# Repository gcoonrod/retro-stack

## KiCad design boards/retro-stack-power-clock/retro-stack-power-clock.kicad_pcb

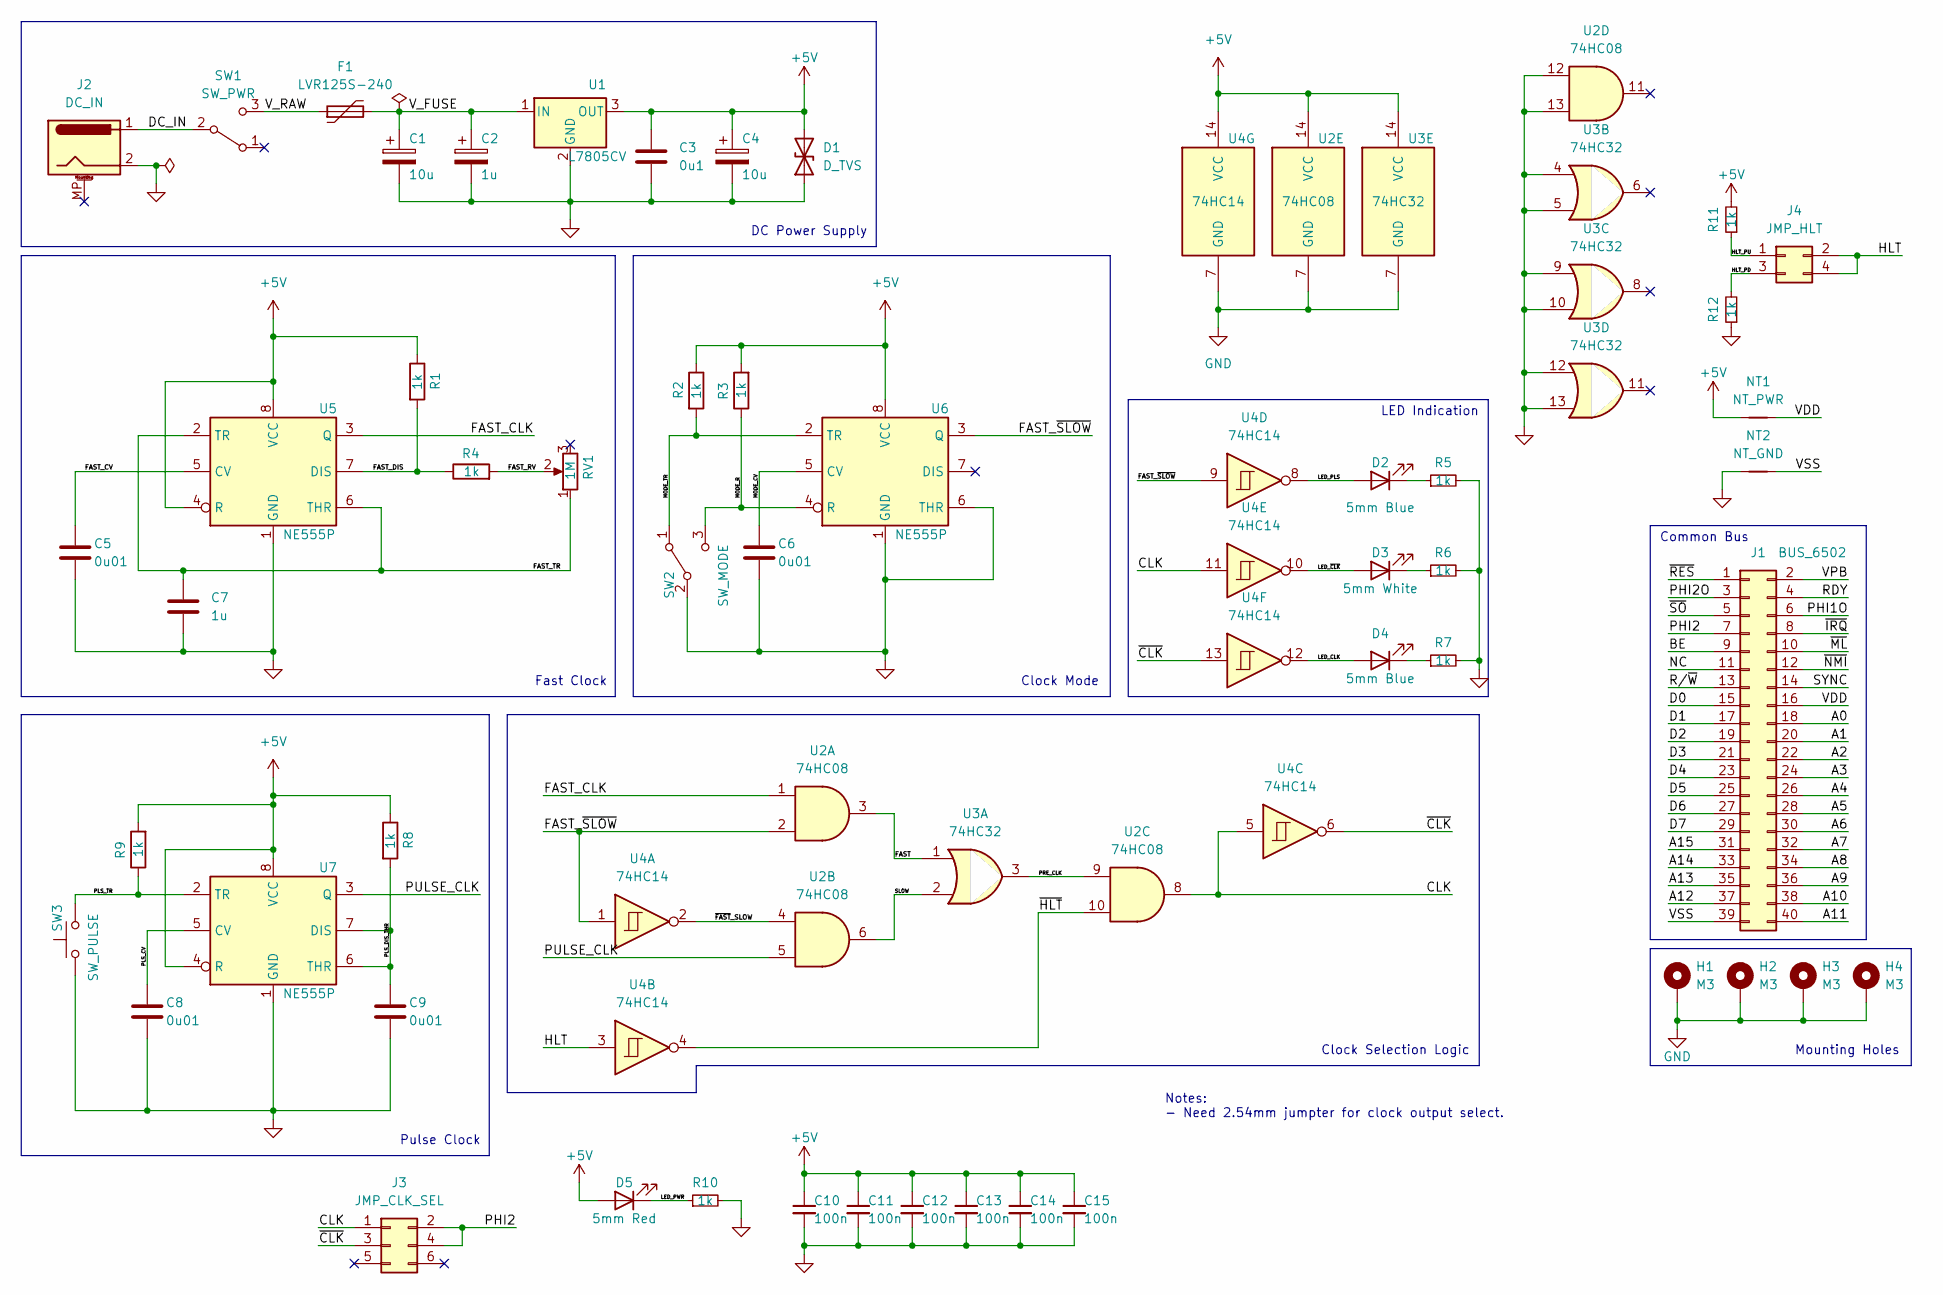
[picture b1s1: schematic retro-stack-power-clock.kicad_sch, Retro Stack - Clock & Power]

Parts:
C1, C4: 10u; CP_Radial_D5.0mm_P2.00mm; Mfr Part 50YXM10MEFR5X11
C2: 1u; CP_Radial_D5.0mm_P2.50mm; Mfr Part TAP105K050SCS
C3: 0u1; C_Rect_L7.0mm_W2.5mm_P5.00mm; Mfr Part K104K15X7RF53H5
C5, C6, C8, C9: 0u01; C_Rect_L7.0mm_W4.5mm_P5.00mm; Mfr Part FG28C0G1H103JNT06
C7: 1u; C_Rect_L4.6mm_W3.8mm_P2.50mm_MKS02_FKP02; Mfr Part FG18X7R1E105KRT06
C10, C11, C12, C13, C14, C15: 100n; C_Rect_L7.0mm_W2.5mm_P5.00mm; Mfr Part K104K15X7RF53H5
D1: D_TVS; D_DO-201_P5.08mm_Vertical_AnodeUp; Mfr Part 1.5KE6.8CA
D2, D4: 5mm Blue; LED_D5.0mm; Mfr Part SSL-LX5093USBD
D3: 5mm White; LED_D5.0mm; Mfr Part SSL-LX5093UWW
D5: 5mm Red; LED_D5.0mm; Mfr Part 151051RS11000
F1: LVR125S-240; LVR125S240; Mfr Part LVR125S-240
H1, H2, H3, H4: M3; MountingHole_3.2mm_M3_ISO7380_Pad
J1: BUS_6502; PinSocket_2x20_P2.54mm_Vertical; Mfr Part 61304021821
J2: DC_IN; BarrelJack_CUI_PJ-063AH_Horizontal; Mfr Part PJ-063AH
J3: JMP_CLK_SEL; PinHeader_2x03_P2.54mm_Vertical; Mfr Part 10129381-906002BLF
J4: JMP_HLT; PinHeader_2x02_P2.54mm_Vertical
NT1: NT_PWR; NetTie-2_SMD_Pad2.0mm
NT2: NT_GND; NetTie-2_SMD_Pad2.0mm
R1, R2, R3, R4, R5, R6, R7, R8, R9, R10, R11, R12: 1k; R_Axial_DIN0207_L6.3mm_D2.5mm_P10.16mm_Horizontal; Mfr Part MFR-25FBF52-1K
RV1: 1M; Potentiometer_Bourns_PTV09A-2_Single_Horizontal; Mfr Part PTV09A-2025F-B105
SW1: SW_PWR; EG1213; Mfr Part EG1213
SW2: SW_MODE; LC1258EENP1RLGR; Mfr Part LC1258EENP1RLGR
SW3: SW_PULSE; SW_Tactile_SPST_Angled_PTS645Vx58-2LFS; Mfr Part TS11-674-73-BK-100-RA-D
U1: L7805CV; TO-220-3_Horizontal_TabUp; Mfr Part L7805CV
U2: 74HC08; DIP-14_W7.62mm_Socket_LongPads; Mfr Part SN74HC08N
U3: 74HC32; DIP-14_W7.62mm_Socket_LongPads; Mfr Part SN74HC32N
U4: 74HC14; DIP-14_W7.62mm_Socket_LongPads; Mfr Part SN74HC14AN
U5, U6, U7: NE555P; DIP-8_W7.62mm_LongPads; Mfr Part NE555P

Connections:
+5V: C3.1, C4.1, C10.1, C11.1, C12.1, C13.1, C14.1, C15.1, D1.2 (A2), D5.2 (A), NT1.1, R1.1, R2.1, R3.2, R8.1, R9.2, R11.2, U1.3 (OUT), U2.14 (VCC), U3.14 (VCC), U4.14 (VCC), U5.4 (R), U5.8 (VCC), U6.8 (VCC), U7.4 (R), U7.8 (VCC)
/A0: J1.18
/A1: J1.20
/A2: J1.22
/A3: J1.24
/A4: J1.26
/A5: J1.28
/A6: J1.30
/A7: J1.32
/A8: J1.34
/A9: J1.36
/A10: J1.38
/A11: J1.40
/A12: J1.37
/A13: J1.35
/A14: J1.33
/A15: J1.31
/BE: J1.9
/CLK: J3.1, U2.8, U4.5, U4.11
/D0: J1.15
/D1: J1.17
/D2: J1.19
/D3: J1.21
/D4: J1.23
/D5: J1.25
/D6: J1.27
/D7: J1.29
/DC_IN: J2.1, SW1.2 (B)
/FAST: U2.3, U3.1
/FAST_CLK: U2.1, U5.3 (Q)
/FAST_CV: C5.1, U5.5 (CV)
/FAST_DIS: R1.2, R4.1, U5.7 (DIS)
/FAST_RV: R4.2, RV1.2
/FAST_TR: C7.1, RV1.1, U5.2 (TR), U5.6 (THR)
/FAST_~SLOW: U2.2, U4.1, U4.9, U6.3 (Q)
/HLT: J4.2, J4.4, U4.3
/HLT_PD: J4.3, R12.2
/HLT_PU: J4.1, R11.1
/LED_CLK: D4.2 (A), U4.12
/LED_PLS: D2.2 (A), U4.8
/LED_PWR: D5.1 (K), R10.1
/LED_~CLK: D3.2 (A), U4.10
/MODE_CV: C6.1, U6.5 (CV)
/MODE_R: R3.1, SW2.3 (C), U6.4 (R)
/MODE_TR: R2.2, SW2.1 (A), U6.2 (TR)
/NC: J1.11
/PHI1O: J1.6
/PHI2: J1.7, J3.2, J3.4
/PHI2O: J1.3
/PLS_CV: C8.1, U7.5 (CV)
/PLS_DIS_THR: C9.1, R8.2, U7.6 (THR), U7.7 (DIS)
/PLS_TR: R9.1, SW3.2, U7.2 (TR)
/PRE_CLK: U2.9, U3.3
/PULSE_CLK: U2.5, U7.3 (Q)
/RDY: J1.4
/R/~W: J1.13
/SLOW: U2.6, U3.2
/SYNC: J1.14
/VDD: J1.16, NT1.2
/VPB: J1.2
/VSS: J1.39, NT2.2
/V_FUSE: C1.1, C2.1, F1.2, U1.1 (IN)
/V_RAW: F1.1, SW1.3 (C)
/~CLK: J3.3, U4.6, U4.13
/~FAST_SLOW: U2.4, U4.2
/~HLT: U2.10, U4.4
/~IRQ: J1.8
/~ML: J1.10
/~NMI: J1.12
/~RES: J1.1
/~SO: J1.5
GND: C1.2, C2.2, C3.2, C4.2, C5.2, C6.2, C7.2, C8.2, C9.2, C10.2, C11.2, C12.2, C13.2, C14.2, C15.2, D1.1 (A1), H1.1, H2.1, H3.1, H4.1, J2.2, NT2.1, R5.2, R6.2, R7.2, R10.2, R12.1, SW2.2 (B), SW3.1, U1.2 (GND), U2.7 (GND), U2.12, U2.13, U3.4, U3.5, U3.7 (GND), U3.9, U3.10, U3.12, U3.13, U4.7 (GND), U5.1 (GND), U6.1 (GND), U6.6 (THR), U7.1 (GND)
unnamed: D2.1 (K), R5.1
unnamed: D3.1 (K), R6.1
unnamed: D4.1 (K), R7.1

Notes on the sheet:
Pulse Clock
Fast Clock
Common Bus
LED Indication
Notes: - Need 2.54mm jumpter for clock output select.
DC Power Supply
Mounting Holes
Clock Mode
Clock Selection Logic

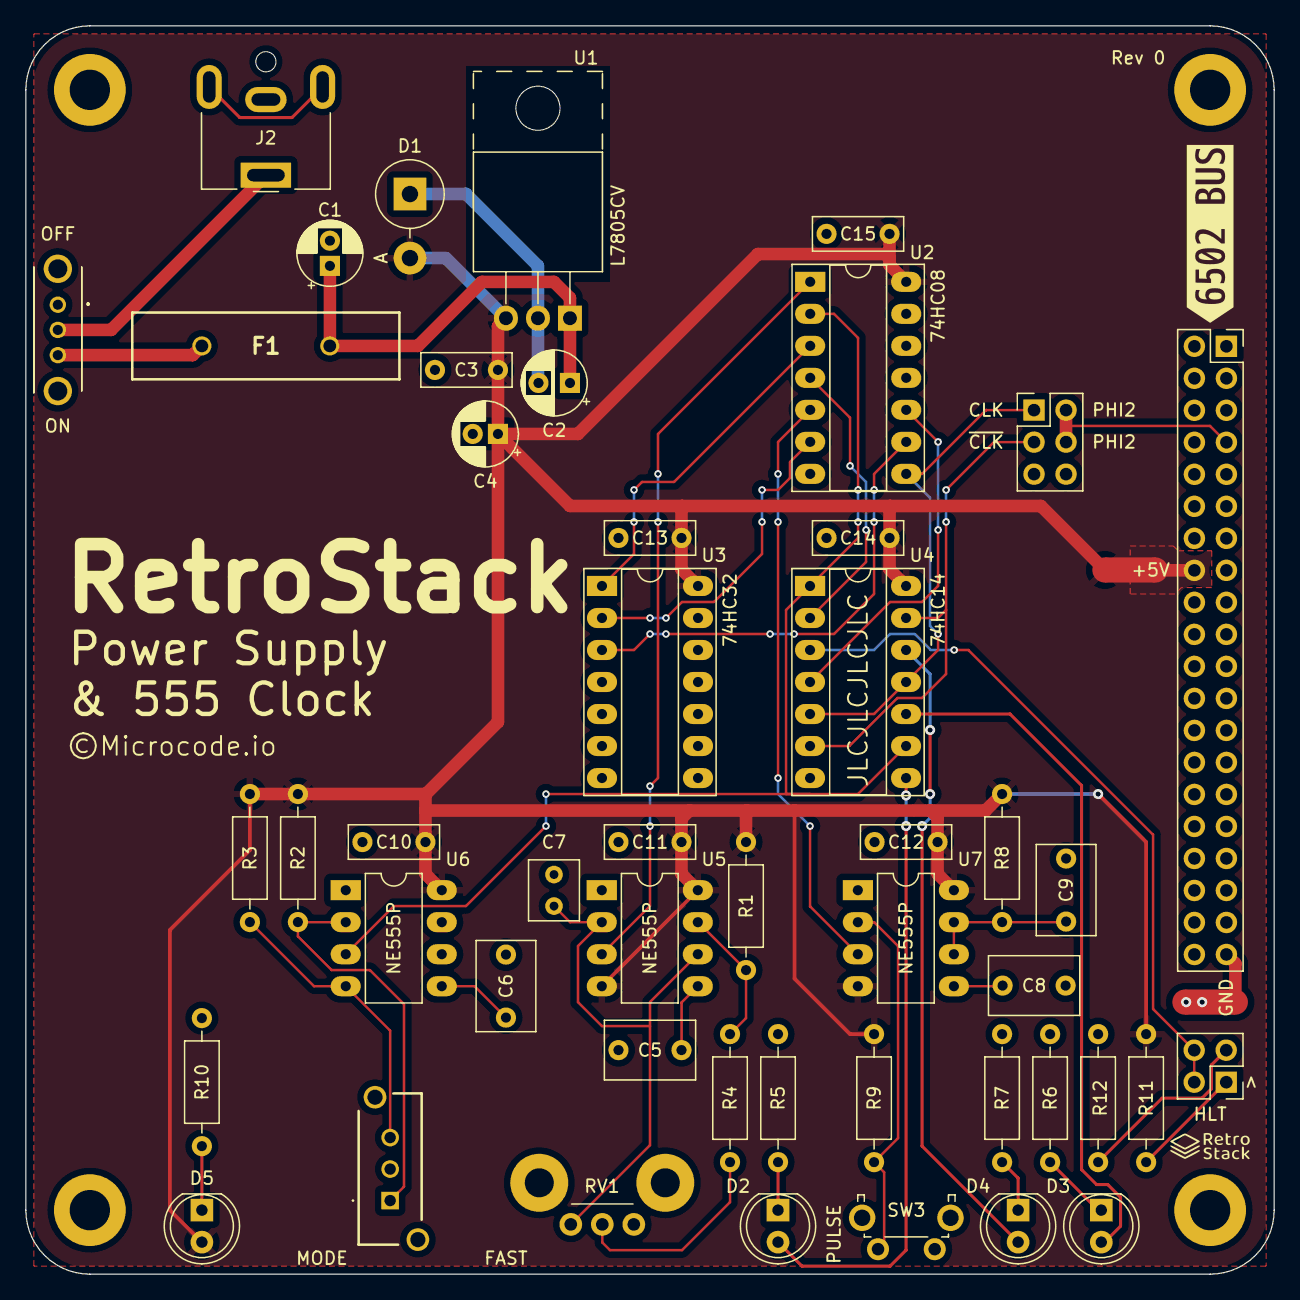
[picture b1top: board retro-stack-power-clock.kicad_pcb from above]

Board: 2 copper layers, 99.1 x 99.1 mm, 55 parts (0 on the bottom side), 38 nets.

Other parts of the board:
kibuzzard-642888DE: G***; kibuzzard-642888DE

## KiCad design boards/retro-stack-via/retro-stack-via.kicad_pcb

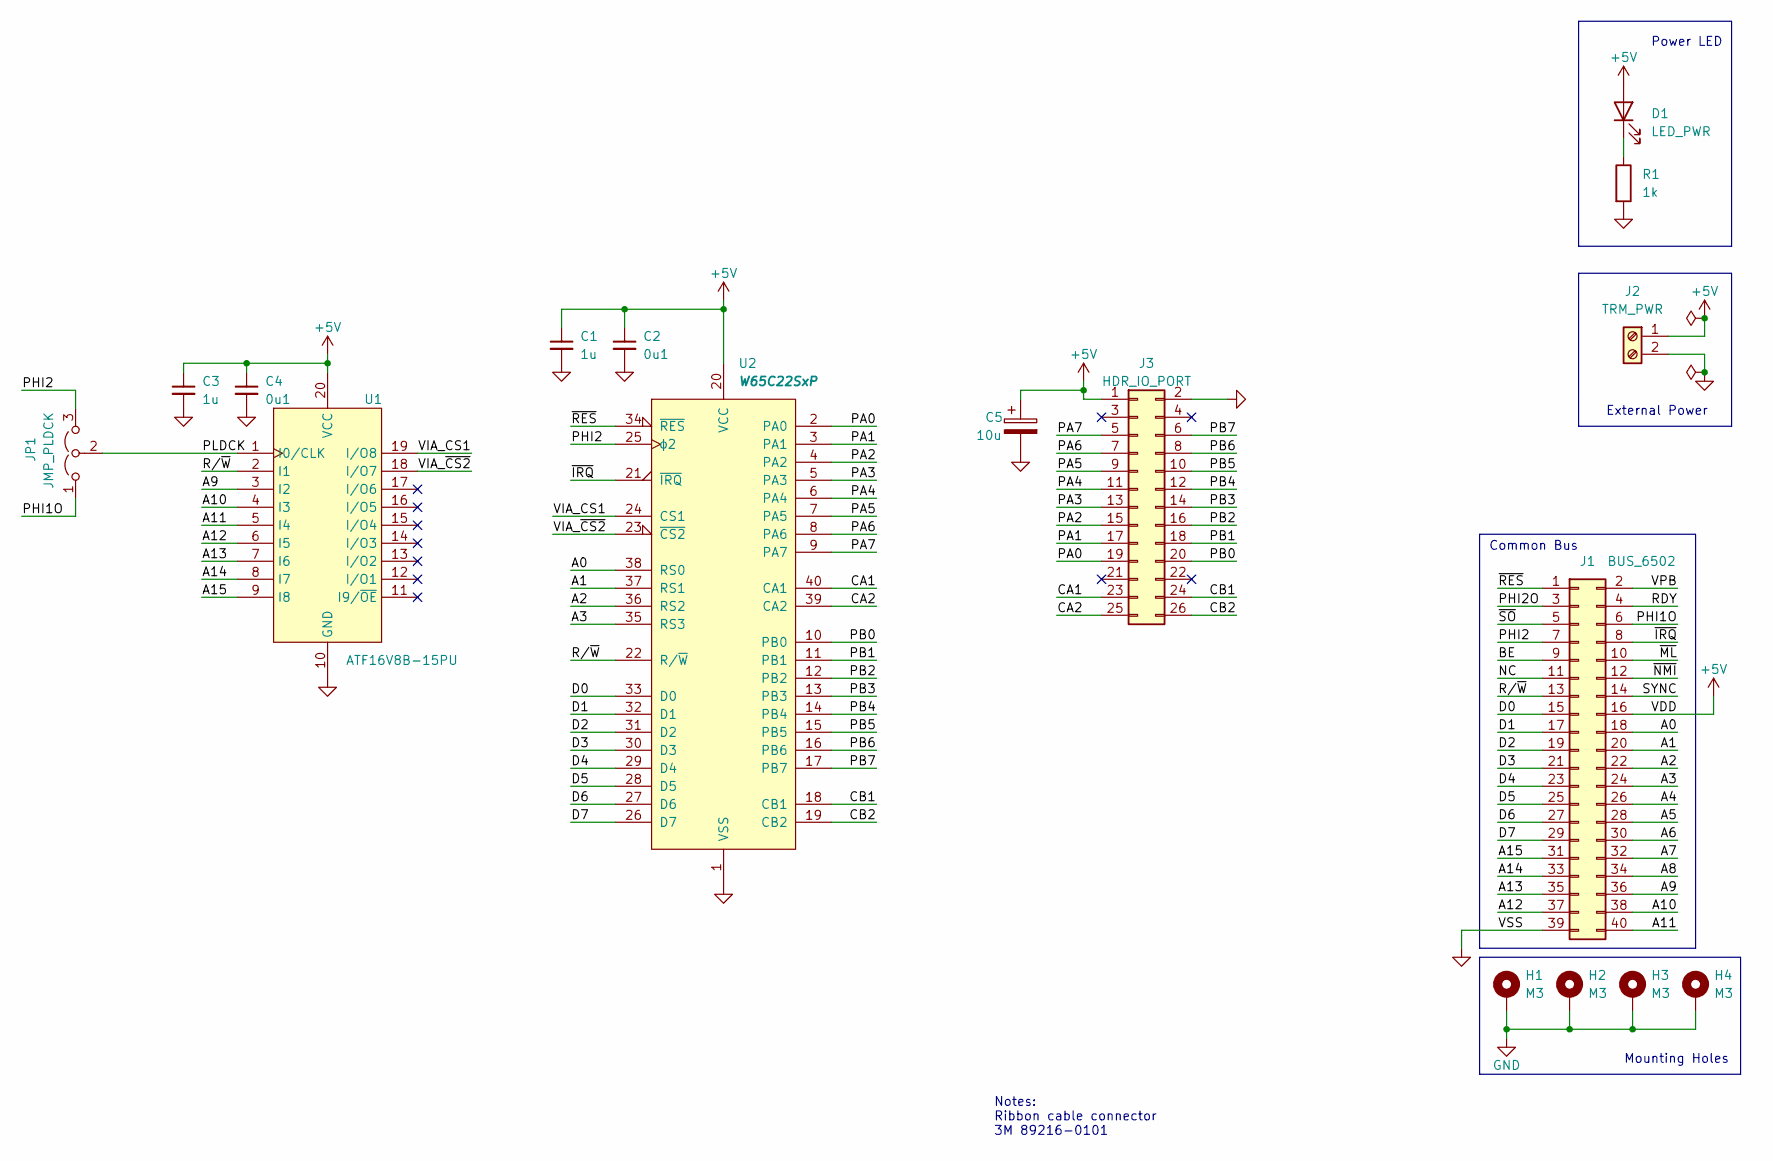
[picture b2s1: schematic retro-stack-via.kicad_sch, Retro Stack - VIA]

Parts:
C1, C3: 1u; C_Rect_L4.0mm_W2.5mm_P2.50mm; Mfr Part FA18X7R1E105KRU06
C2, C4: 0u1; C_Rect_L4.0mm_W2.5mm_P2.50mm; Mfr Part RCER71E104K0A2H03B
C5: 10u; CP_Radial_D5.0mm_P2.50mm
D1: LED_PWR; LED_D5.0mm
H1, H2, H3, H4: M3; MountingHole_3.2mm_M3_ISO7380_Pad
J1: BUS_6502; PinSocket_2x20_P2.54mm_Vertical
J2: TRM_PWR; TerminalBlock_Phoenix_MPT-0,5-2-2.54_1x02_P2.54mm_Horizontal; Mfr Part 1725656
J3: HDR_IO_PORT; IDC-Header_2x13_P2.54mm_Vertical; Mfr Part 30326-6002HB
JP1: JMP_PLDCK; PinHeader_1x03_P2.54mm_Vertical; Mfr Part M7581-05
R1: 1k; R_Axial_DIN0204_L3.6mm_D1.6mm_P5.08mm_Horizontal
U1: ATF16V8B-15PU; DIP-20_W7.62mm_Socket_LongPads; Mfr Part ATF16V8B-15PU
U2: W65C22SxP; DIP-40_W15.24mm_Socket_LongPads

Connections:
+5V: C1.1, C2.1, C3.1, C4.1, C5.1, D1.2 (A), J1.16, J2.1, J3.1, U1.20 (VCC), U2.20 (VCC)
/A0: J1.18, U2.38 (RS0)
/A1: J1.20, U2.37 (RS1)
/A2: J1.22, U2.36 (RS2)
/A3: J1.24, U2.35 (RS3)
/A4: J1.26
/A5: J1.28
/A6: J1.30
/A7: J1.32
/A8: J1.34
/A9: J1.36, U1.3 (I2)
/A10: J1.38, U1.4 (I3)
/A11: J1.40, U1.5 (I4)
/A12: J1.37, U1.6 (I5)
/A13: J1.35, U1.7 (I6)
/A14: J1.33, U1.8 (I7)
/A15: J1.31, U1.9 (I8)
/BE: J1.9
/CA1: J3.23, U2.40 (CA1)
/CA2: J3.25, U2.39 (CA2)
/CB1: J3.24, U2.18 (CB1)
/CB2: J3.26, U2.19 (CB2)
/D0: J1.15, U2.33 (D0)
/D1: J1.17, U2.32 (D1)
/D2: J1.19, U2.31 (D2)
/D3: J1.21, U2.30 (D3)
/D4: J1.23, U2.29 (D4)
/D5: J1.25, U2.28 (D5)
/D6: J1.27, U2.27 (D6)
/D7: J1.29, U2.26 (D7)
/NC: J1.11
/PA0: J3.19, U2.2 (PA0)
/PA1: J3.17, U2.3 (PA1)
/PA2: J3.15, U2.4 (PA2)
/PA3: J3.13, U2.5 (PA3)
/PA4: J3.11, U2.6 (PA4)
/PA5: J3.9, U2.7 (PA5)
/PA6: J3.7, U2.8 (PA6)
/PA7: J3.5, U2.9 (PA7)
/PB0: J3.20, U2.10 (PB0)
/PB1: J3.18, U2.11 (PB1)
/PB2: J3.16, U2.12 (PB2)
/PB3: J3.14, U2.13 (PB3)
/PB4: J3.12, U2.14 (PB4)
/PB5: J3.10, U2.15 (PB5)
/PB6: J3.8, U2.16 (PB6)
/PB7: J3.6, U2.17 (PB7)
/PHI1O: J1.6, JP1.1 (A)
/PHI2: J1.7, JP1.3 (B), U2.25 (ϕ2)
/PHI2O: J1.3
/PLDCK: JP1.2 (C), U1.1 (I0/CLK)
/RDY: J1.4
/R/~W: J1.13, U1.2 (I1), U2.22 (R/~W)
/SYNC: J1.14
/VIA_CS1: U1.19 (I/O8), U2.24 (CS1)
/VIA_~CS2: U1.18 (I/O7), U2.23 (~CS2)
/VPB: J1.2
/~IRQ: J1.8, U2.21 (~IRQ)
/~ML: J1.10
/~NMI: J1.12
/~RES: J1.1, U2.34 (~RES)
/~SO: J1.5
GND: C1.2, C2.2, C3.2, C4.2, C5.2, H1.1, H2.1, H3.1, H4.1, J1.39, J2.2, J3.2, R1.2, U1.10 (GND), U2.1 (VSS)
unnamed: D1.1 (K), R1.1

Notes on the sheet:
Notes: Ribbon cable connector 3M 89216-0101
External Power
Common Bus
Power LED
Mounting Holes

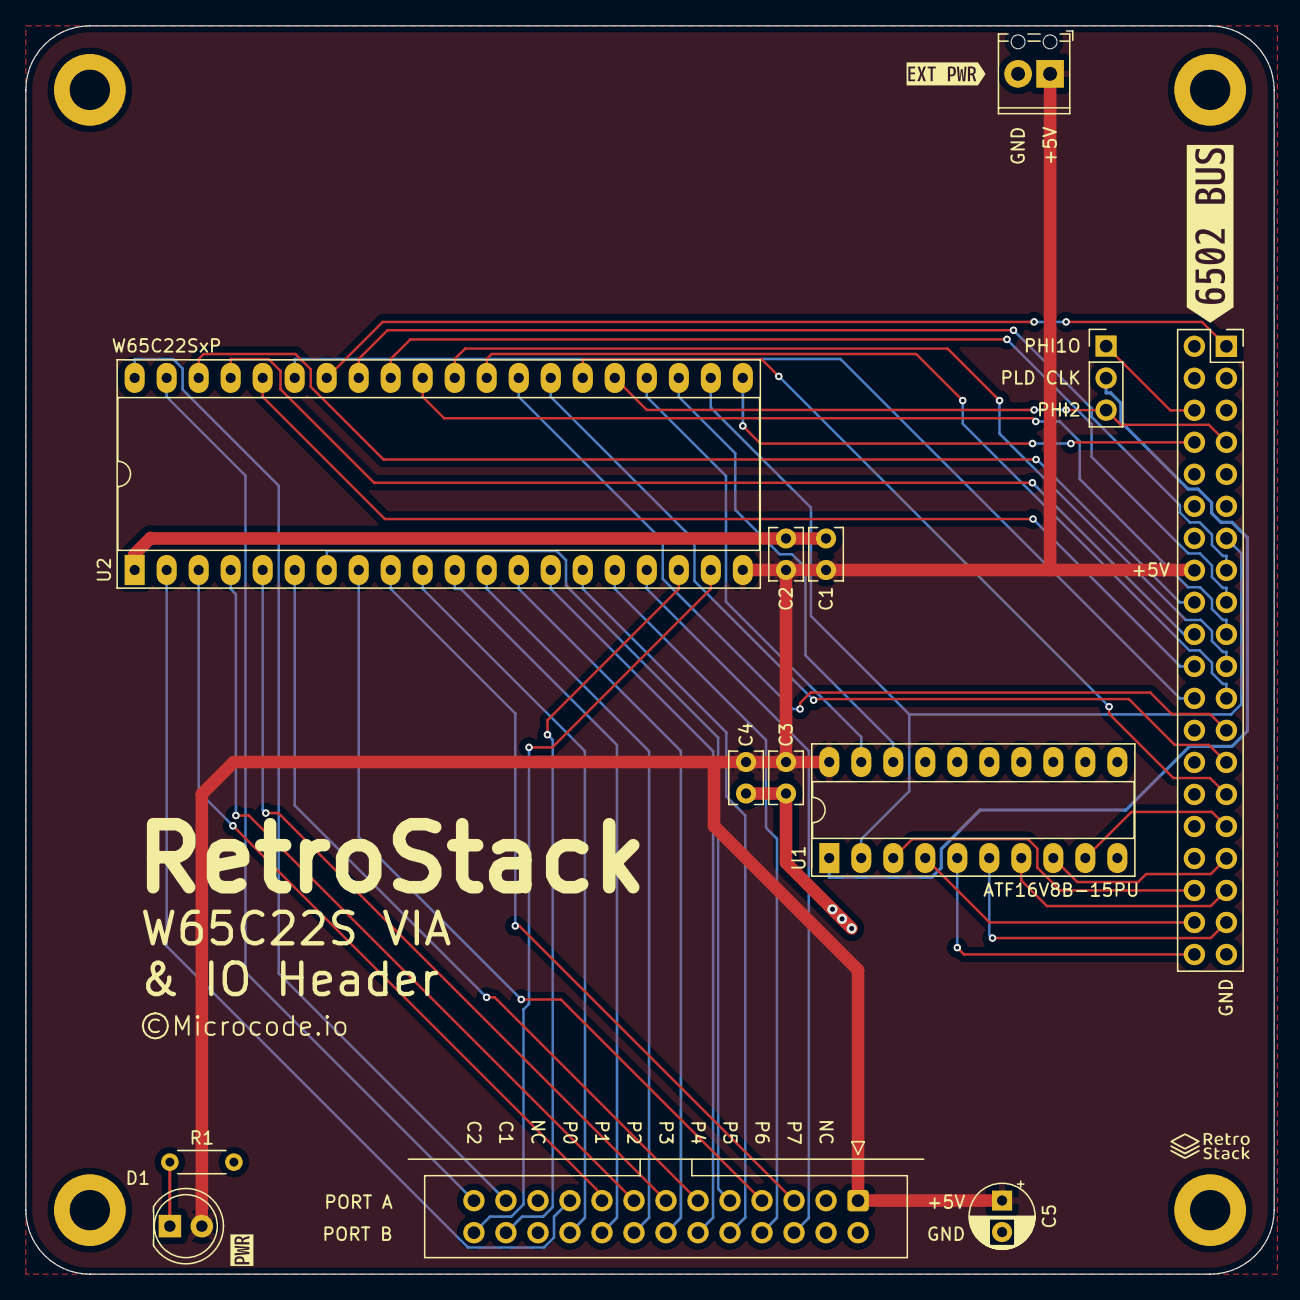
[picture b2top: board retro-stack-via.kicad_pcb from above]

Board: 2 copper layers, 99.1 x 99.1 mm, 20 parts (0 on the bottom side), 50 nets.

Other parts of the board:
kibuzzard-642C36EF: G***; kibuzzard-642C36EF
kibuzzard-642C367F: G***; kibuzzard-642C367F
kibuzzard-642888DE: G***; kibuzzard-642888DE

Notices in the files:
boards/retro-stack-power-clock/retro-stack-power-clock.kicad_pcb:
©Microcode.io
